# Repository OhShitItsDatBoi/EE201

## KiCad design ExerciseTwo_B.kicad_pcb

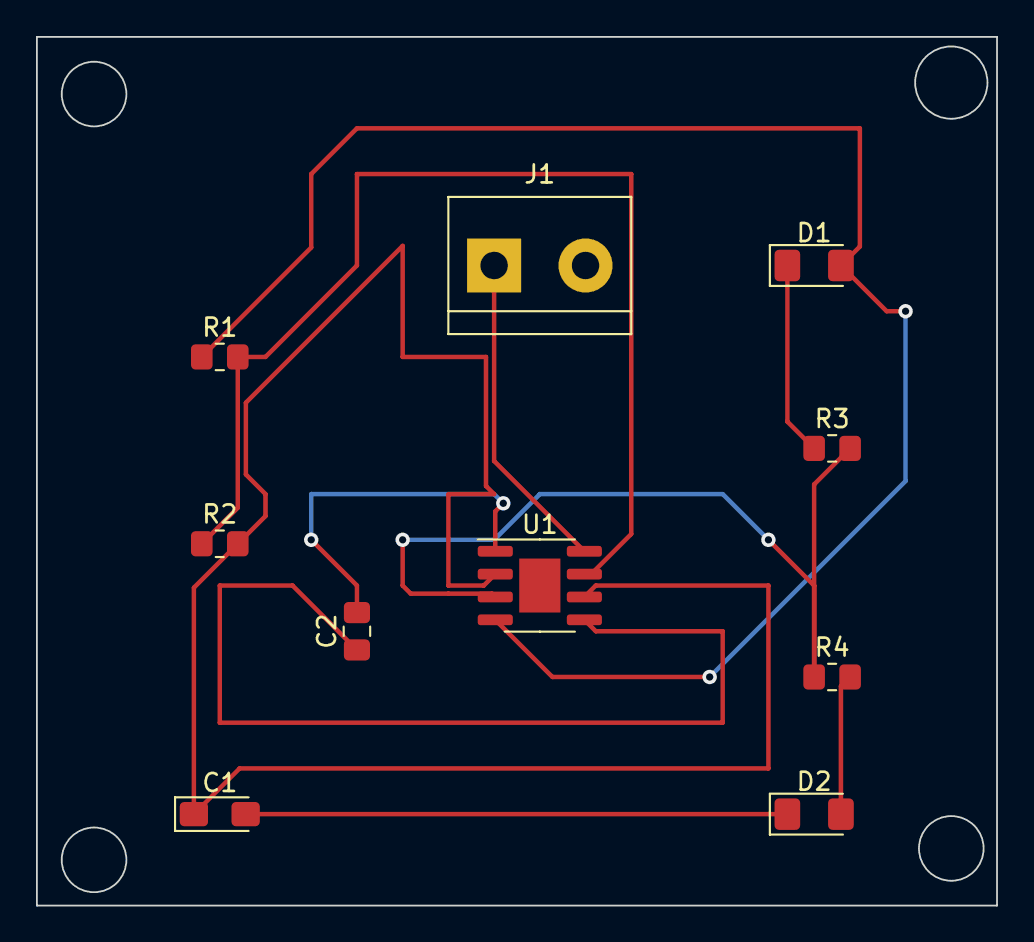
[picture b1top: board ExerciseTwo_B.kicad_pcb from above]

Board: 2 copper layers, 53.3 x 48.3 mm, 10 parts (0 on the bottom side), 9 nets.

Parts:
C1: 10 uF; CP_EIA-3216-18_Kemet-A_Pad1.58x1.35mm_HandSolder
C2: 0.01 uF; C_0805_2012Metric_Pad1.18x1.45mm_HandSolder
D1, D2: LED; LED_1206_3216Metric_Pad1.42x1.75mm_HandSolder
J1: Conn_01x02_Male; TerminalBlock_bornier-2_P5.08mm
R1, R3, R4: 1k; R_0805_2012Metric_Pad1.20x1.40mm_HandSolder
R2: 10k; R_0805_2012Metric_Pad1.20x1.40mm_HandSolder
U1: NE555D; SOIC-8-1EP_3.9x4.9mm_P1.27mm_EP2.29x3mm

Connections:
/+9V: D1.2 (A), R1.1, U1.4 (R)
/Pin 2: C1.1, R2.2, U1.2 (TR), U1.6 (THR)
/Pin 7: R1.2, R2.1, U1.7 (DIS)
GND: C1.2, C2.2, D2.1 (K), J1.2, U1.1 (GND)
unnamed: C2.1, U1.5 (CV)
unnamed: D1.1 (K), R3.1
unnamed: D2.2 (A), R4.2
unnamed: J1.1, U1.8 (VCC)
unnamed: R3.2, R4.1, U1.3 (Q)

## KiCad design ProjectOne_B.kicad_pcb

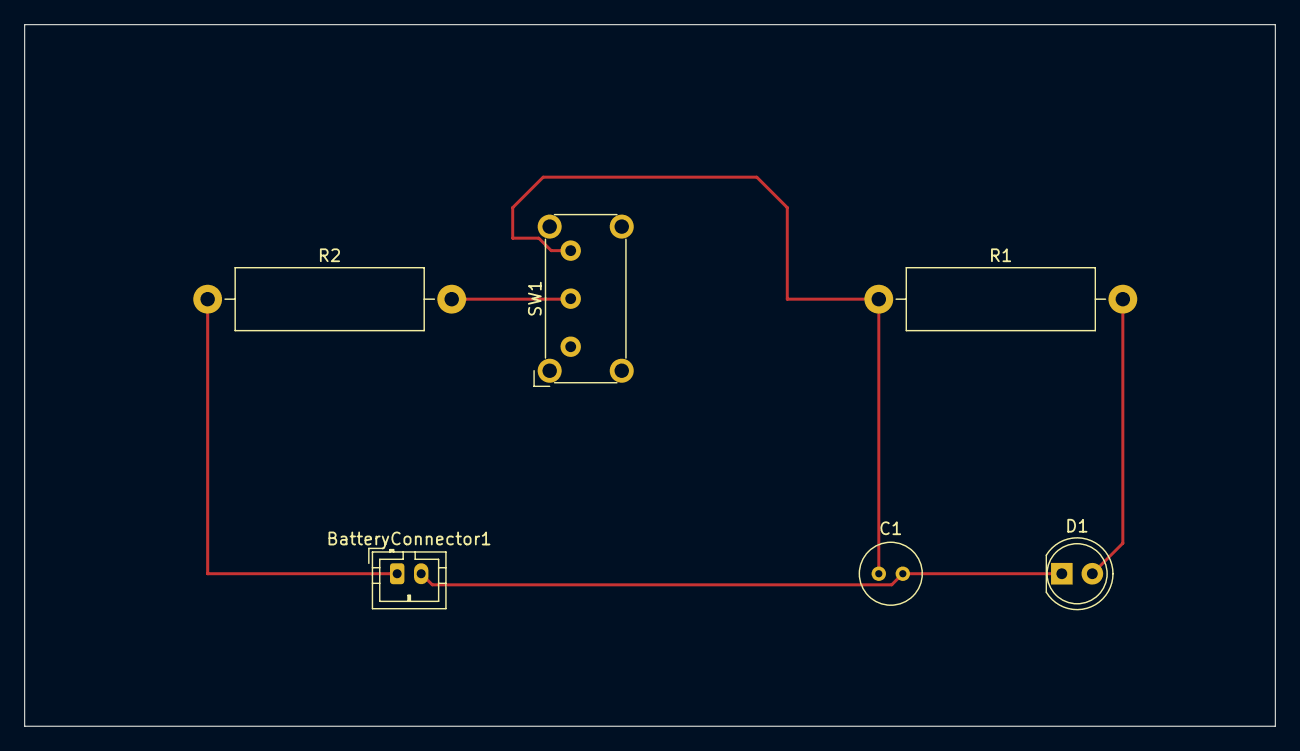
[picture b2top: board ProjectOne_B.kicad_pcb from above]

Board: 2 copper layers, 104.1 x 58.4 mm, 6 parts (0 on the bottom side), 5 nets.

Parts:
BatteryConnector1: 9V; JST_PH_B2B-PH-K_1x02_P2.00mm_Vertical
C1: 4.7uF; C_Radial_D5.0mm_H5.0mm_P2.00mm
D1: LED; LED_D5.0mm
R1: 20k; R_Axial_DIN0516_L15.5mm_D5.0mm_P20.32mm_Horizontal
R2: 2.2k; R_Axial_DIN0516_L15.5mm_D5.0mm_P20.32mm_Horizontal
SW1: SW_SPDT; SW_E-Switch_EG1224_SPDT_Angled

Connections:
unnamed: BatteryConnector1.1, R2.1
unnamed: BatteryConnector1.2, C1.2, D1.1 (K)
unnamed: C1.1, R1.1, SW1.3 (C)
unnamed: D1.2 (A), R1.2
unnamed: R2.2, SW1.2 (B)

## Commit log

2023-01-14 Testing take two
2023-01-21 Arduino Commit Take Two
2023-01-28 PCB Commit Take One
2023-02-10 Soldering Push Take One
2023-02-11 Lab 6 kicad_pcb Files
2023-02-17 Gerber and Drill Files Take One
2023-03-11 Multimeter
    Thanks for everything yall!
